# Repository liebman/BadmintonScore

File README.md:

# Badminton Scoreboard

A simple LED Matrix scoreboard for badminton implemented for fun because some friends host a Badminton party in most years.

## Usage

On power on you hve to choose the game score limit between a normal 21 point game and a short 15 point game.  Use the button on the same side as the game limit you want.  After that a short press on either side button increments the score on that side, a long press decrements the score in case of a mistake.  A short press on the middle button swaps the score from side to side, a long press will reset the score back to 0 and a very long 10-15 seconds will perform a reset allowing you to change the game limit.

[src](src) Contains the code for the Badminton Scoreboard

[ScoreBoard](ScoreBoard) contains the schematic and board designs in Eagle cad.

[3d](3d) contains the STL files for the enclosure.

## Misc Parts

P4 64x32 LED Display w/HUB75 interface

[50 Watt 5v power supply](https://smile.amazon.com/gp/product/B019GYOCMM/ref=ppx_yo_dt_b_search_asin_title?ie=UTF8&psc=1)

3 SPST Buttons

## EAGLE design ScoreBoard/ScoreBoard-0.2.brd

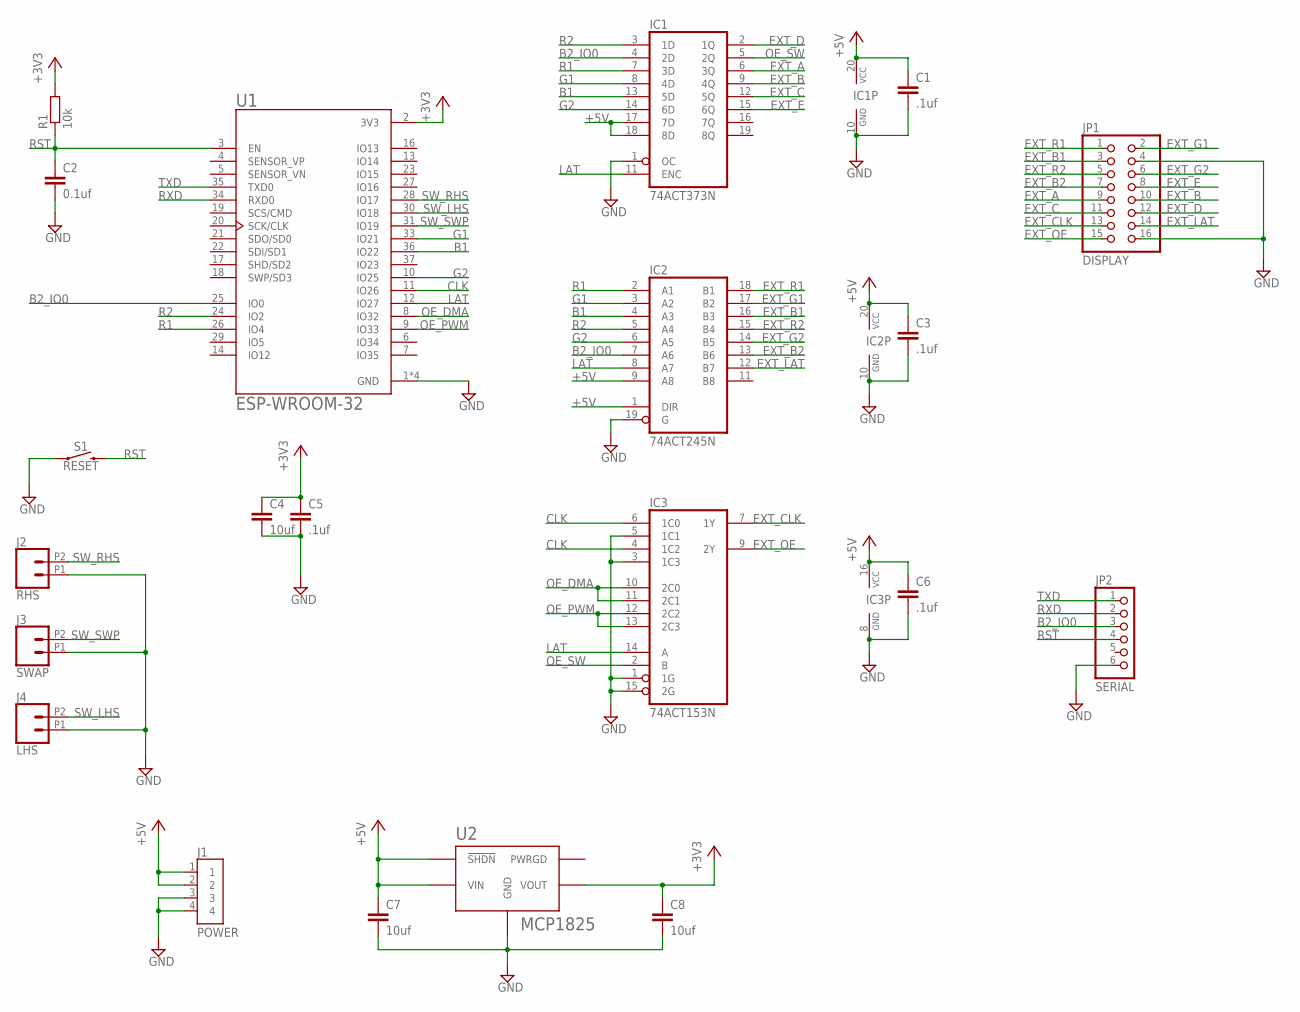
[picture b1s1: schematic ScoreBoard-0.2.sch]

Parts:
C1, C3, C5, C6: .1uf; C025-025X050
C2: 0.1uf; C025-025X050
C4, C7, C8: 10uf; C050-025X075
IC1: 74ACT373N; DIL20
IC2: 74ACT245N; DIL20
IC3: 74ACT153N; DIL16
J1: POWER; TE_1-1123723-4
J2: RHS; 1X02_2.54_SCREWTERM
J3: SWAP; 1X02_2.54_SCREWTERM
J4: LHS; 1X02_2.54_SCREWTERM
JP1: DISPLAY; 2X08
JP2: SERIAL; 1X06/90
R1: 10k; 0204/7
S1: RESET; TACTILE_SWITCH_PTH_6.0MM
U1: ESP-WROOM-32; MODULE_ESP-WROOM-32
U2: MCP1825; SOT-223-5

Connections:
+3V3: C4.1, C5.1, C8.1, R1.2, U1.2 (3V3), U2.P$4 (VOUT)
+5V: C1.1, C3.1, C6.1, C7.1, IC1.17 (7D), IC1.18 (8D), IC1.20 (VCC), IC2.1 (DIR), IC2.9 (A8), IC2.20 (VCC), IC3.16 (VCC), J1.1, J1.2, U2.P$1 (!SHDN), U2.P$2 (VIN)
B1: IC1.13 (5D), IC2.4 (A3), U1.36 (IO22)
B2_IO0: IC1.4 (2D), IC2.7 (A6), JP2.3, U1.25 (IO0)
CLK: IC3.4 (1C2), IC3.6 (1C0), U1.11 (IO26)
EXT_A: IC1.6 (3Q), JP1.9
EXT_B: IC1.9 (4Q), JP1.10
EXT_B1: IC2.16 (B3), JP1.3
EXT_B2: IC2.13 (B6), JP1.7
EXT_C: IC1.12 (5Q), JP1.11
EXT_CLK: IC3.7 (1Y), JP1.13
EXT_D: IC1.2 (1Q), JP1.12
EXT_E: IC1.15 (6Q), JP1.8
EXT_G1: IC2.17 (B2), JP1.2
EXT_G2: IC2.14 (B5), JP1.6
EXT_LAT: IC2.12 (B7), JP1.14
EXT_OE: IC3.9 (2Y), JP1.15
EXT_R1: IC2.18 (B1), JP1.1
EXT_R2: IC2.15 (B4), JP1.5
G1: IC1.8 (4D), IC2.3 (A2), U1.33 (IO21)
G2: IC1.14 (6D), IC2.6 (A5), U1.10 (IO25)
GND: C1.2, C2.2, C3.2, C4.2, C5.2, C6.2, C7.2, C8.2, IC1.1 (OC), IC1.10 (GND), IC2.10 (GND), IC2.19 (G), IC3.1 (1G), IC3.3 (1C3), IC3.5 (1C1), IC3.8 (GND), IC3.15 (2G), J1.3, J1.4, J2.P1 (1), J3.P1 (1), J4.P1 (1), JP1.4, JP1.16, JP2.6, S1.1, U1.1 (GND), U1.1.1 (GND), U1.15 (GND), U1.38 (GND), U2.P$3 (GND), U2.P$6 (GND)
LAT: IC1.11 (ENC), IC2.8 (A7), IC3.14 (A), U1.12 (IO27)
OE_DMA: IC3.10 (2C0), IC3.11 (2C1), U1.8 (IO32)
OE_PWM: IC3.12 (2C2), IC3.13 (2C3), U1.9 (IO33)
OE_SW: IC1.5 (2Q), IC3.2 (B)
R1: IC1.7 (3D), IC2.2 (A1), U1.26 (IO4)
R2: IC1.3 (1D), IC2.5 (A4), U1.24 (IO2)
RST: C2.1, JP2.4, R1.1, S1.3 (2), U1.3 (EN)
RXD: JP2.2, U1.34 (RXD0)
SW_LHS: J4.P2 (2), U1.30 (IO18)
SW_RHS: J2.P2 (2), U1.28 (IO17)
SW_SWP: J3.P2 (2), U1.31 (IO19)
TXD: JP2.1, U1.35 (TXD0)

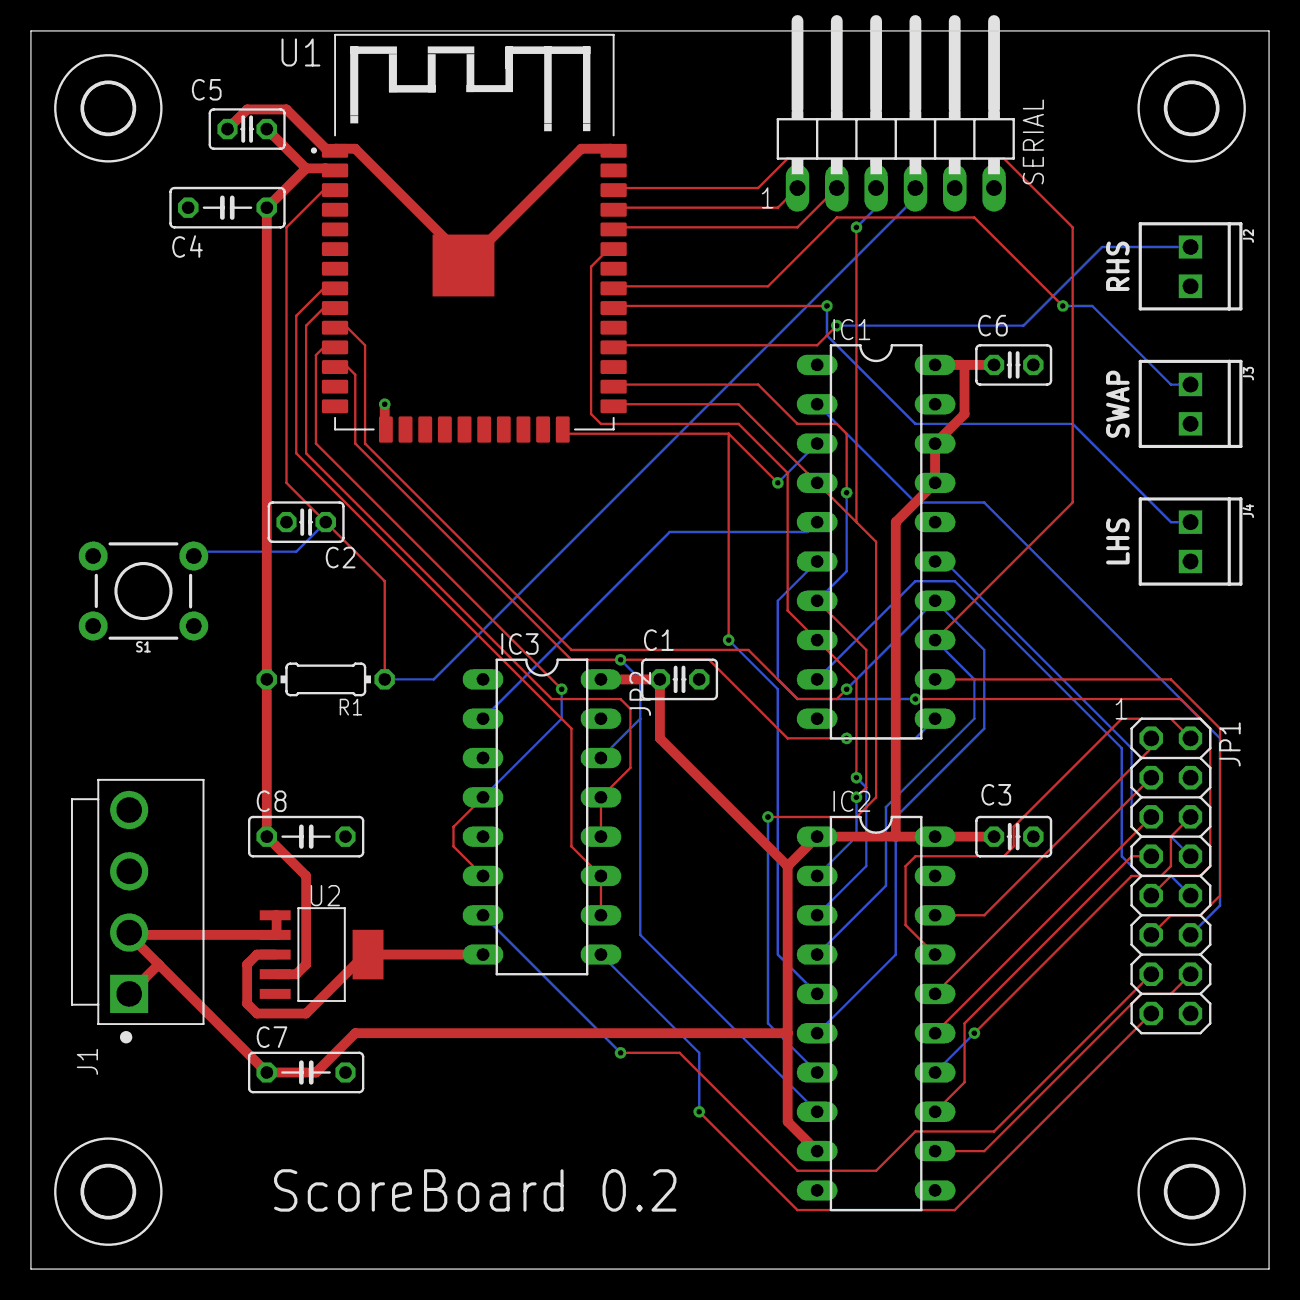
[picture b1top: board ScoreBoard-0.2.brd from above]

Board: 2 copper layers, 80.0 x 80.0 mm, 25 parts (0 on the bottom side), 34 nets.

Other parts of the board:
U$1, U$2, U$3, U$4: 3,2

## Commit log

2021-01-17 initial checkin
2021-01-17 upgrade libs
2021-01-17 Initial README
2021-01-17 update README - add build status

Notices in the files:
parts and their libraries:
SparkFun-Switches: Licensing: Creative Commons ShareAlike 4.0 International - https://creativecommons.org/licenses/by-sa/4.0
